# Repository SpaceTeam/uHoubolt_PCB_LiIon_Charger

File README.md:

# uHoubolt LiIon Charger

Small sized PCB (19mm x 20mm). Used to control and monitor the charging process of a connected LiIon Battery. Soldered to the PMU via edge connectors. Most of the connectors serve a controling function to check the different circuits of the board.

## Features
- Edge connectors
- LED charging state indicator
- Footprint for the connecting PCB
- Known Issues
- The PCB is very noisy
- Did not properly work during EuRoC

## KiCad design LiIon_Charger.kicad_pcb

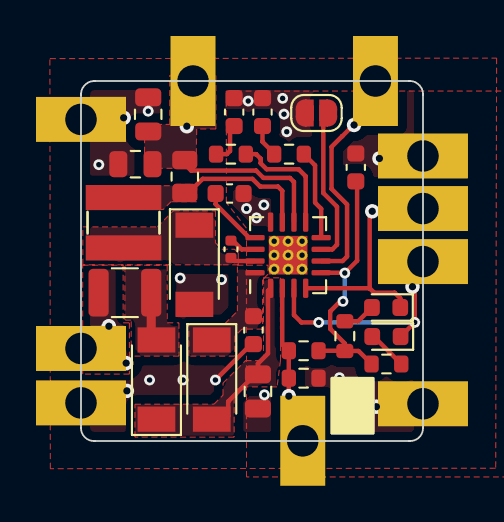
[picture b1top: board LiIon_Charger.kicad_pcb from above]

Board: 2 copper layers, 19.0 x 20.0 mm, 35 parts (0 on the bottom side), 22 nets.

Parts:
C1, C8, C9: 22u; C_0805_2012Metric
C2, C3: 22u; C_0603_1608Metric
C4: 100n; C_0603_1608Metric
C5: 100n; C_0402_1005Metric
C6, C7: 2.2n; C_0603_1608Metric
D1, D4, D5: PMEG3050EP; D_SOD-128
D2, D3: LED; LED_0603_1608Metric
F1: Fuse_Small; R_1210_3225Metric
H1, H2, H3, H4: MountingHole_Pad; Edge_Connector
JP1: SolderJumper_2_Open; SolderJumper-2_P1.3mm_Open_RoundedPad1.0x1.5mm
L1: 4.7u; SRN4018TA-4R7M
R1, R2: 10k; R_0603_1608Metric
R3, R4: 120; R_0603_1608Metric
R5: 750; R_0603_1608Metric
R6: 2.61k; R_0603_1608Metric
R7: 200m; R_0805_2012Metric
U1: MP26123; QFN-16-1EP_4x4mm_P0.65mm_EP2.15x2.15mm_ThermalVias
j1, j2, j3, j4, j5, j6: Conn_01x01; Edge_Connector

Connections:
/Battery: C8.1, C9.1, R7.1, U1.10 (BATT), j6.1
/Charger: F1.1, j1.1
/NTC: R1.2, R2.1, U1.2 (NTC), j2.1
/~ACOK: D2.1 (K), U1.3 (~ACOK), j3.1
/~CHGOK: D3.1 (K), U1.4 (~CHGOK), j4.1
GND: C1.2, C2.2, C3.2, C4.2, C6.2, C7.2, C8.2, C9.2, D5.2 (A), H1.1, H2.1, H3.1, H4.1, JP1.2 (B), R2.2, U1.12 (GND)
unnamed: C1.1, D1.1 (K), D4.2 (A), U1.1 (VCC)
unnamed: C2.1, R1.1, R3.1, R4.1, U1.5 (VREF33)
unnamed: C3.1, D4.1 (K), U1.16 (VIN)
unnamed: C4.1, U1.13 (TMR)
unnamed: C5.1, D5.1 (K), L1.1, U1.15 (SW)
unnamed: C5.2, U1.14 (BST)
unnamed: C6.1, R6.1
unnamed: C7.1, R5.1
unnamed: D1.2 (A), F1.2
unnamed: D2.2 (A), R3.2
unnamed: D3.2 (A), R4.2
unnamed: JP1.1 (A), U1.7 (CELLS)
unnamed: L1.2, R7.2, U1.11 (CSP)
unnamed: R5.2, U1.9 (COMPI)
unnamed: R6.2, U1.8 (COMPV)
unnamed: U1.6 (~EN), j5.1

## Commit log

2022-08-20 Updated version
    Added planes and vias
2022-08-29 V1 Ordered
2023-01-22 Add license
